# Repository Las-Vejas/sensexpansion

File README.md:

# sensexpansion

This is an expansion module for the [Hackxpansion console](https://github.com/hackclub/hackxpansion). This module provides the console with different information like temperature, humidity, rotation, and others.
The module consists of the **BME280** temperature and humidity sensor and the **LIS3DH** accelerometer.

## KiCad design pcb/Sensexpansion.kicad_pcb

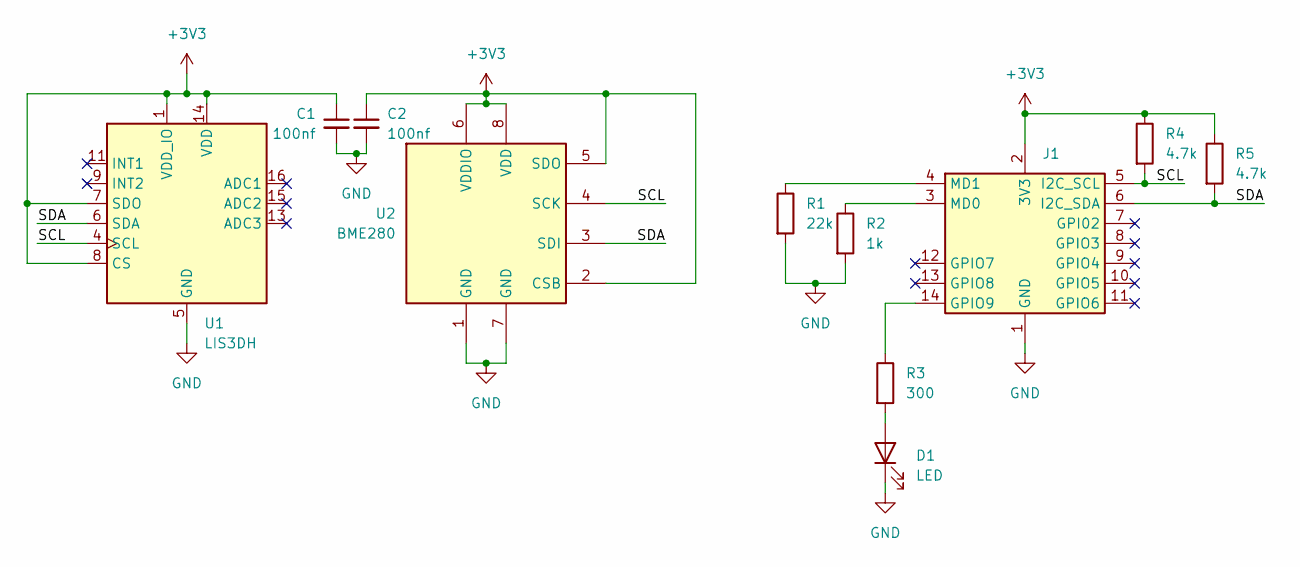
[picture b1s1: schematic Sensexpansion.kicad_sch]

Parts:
C1, C2: 100nf; C_0402_1005Metric; LCSC Part # C60474
D1: LED; LED_0402_1005Metric; LCSC Part # C20608782
J1: Male_Module
R1: 22k; R_0402_1005Metric; LCSC Part # C140179
R2: 1k; R_0402_1005Metric; LCSC Part # C140197
R3: 300; R_0402_1005Metric; LCSC Part # C25102
R4, R5: 4.7k; R_0402_1005Metric; LCSC Part # C140158
U1: LIS3DH; LGA-16_3x3mm_P0.5mm_LayoutBorder3x5y; LCSC Part # C15134
U2: BME280; Bosch_LGA-8_2.5x2.5mm_P0.65mm_ClockwisePinNumbering; LCSC Part # C92489

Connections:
+3V3: C1.1, C2.1, J1.2 (3V3), R4.1, R5.1, U1.1 (VDD_IO), U1.7 (SDO), U1.8 (CS), U1.14 (VDD), U2.2 (CSB), U2.5 (SDO), U2.6 (VDDIO), U2.8 (VDD)
/SCL: J1.5 (I2C_SCL), R4.2, U1.4 (SCL), U2.4 (SCK)
/SDA: J1.6 (I2C_SDA), R5.2, U1.6 (SDA), U2.3 (SDI)
GND: C1.2, C2.2, D1.1 (K), J1.1 (GND), R1.2, R2.2, U1.5 (GND), U1.10 (GND), U1.12 (GND), U2.1 (GND), U2.7 (GND)
unnamed: D1.2 (A), R3.2
unnamed: J1.14 (GPIO9), R3.1
unnamed: J1.3 (MD0), R2.1
unnamed: J1.4 (MD1), R1.1

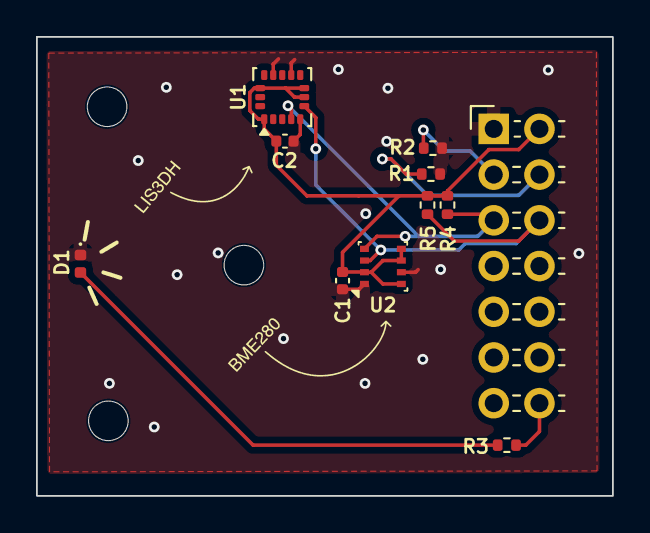
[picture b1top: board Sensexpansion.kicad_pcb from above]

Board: 2 copper layers, 32.0 x 25.5 mm, 11 parts (0 on the bottom side), 8 nets.

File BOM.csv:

Reference,Price,Qty,Value,LCSC Part #
"C1,C2",0.50 $US,2,100nf,C60474
D1,0.69 $US,1,LED,C20608782
J1,0.00 $US,1,N/A,N/A
R1,0.13 $US,1,22k,C140179
R2,0.15 $US,1,1k,C140197
R3,0.21 $US,1,300,C25102
"R4,R5",0.14 $US,2,4.7k,C140158
U1,1.88 $US,1,LIS3DH,C15134
U2,7.13 $US,1,BME280,C92489
PCB,4.00 $US,5,N/A,N/A
Stencil,3.07 $US,1,N/A,N/A
TOTAL,17.90 $US,,N/A,N/A
